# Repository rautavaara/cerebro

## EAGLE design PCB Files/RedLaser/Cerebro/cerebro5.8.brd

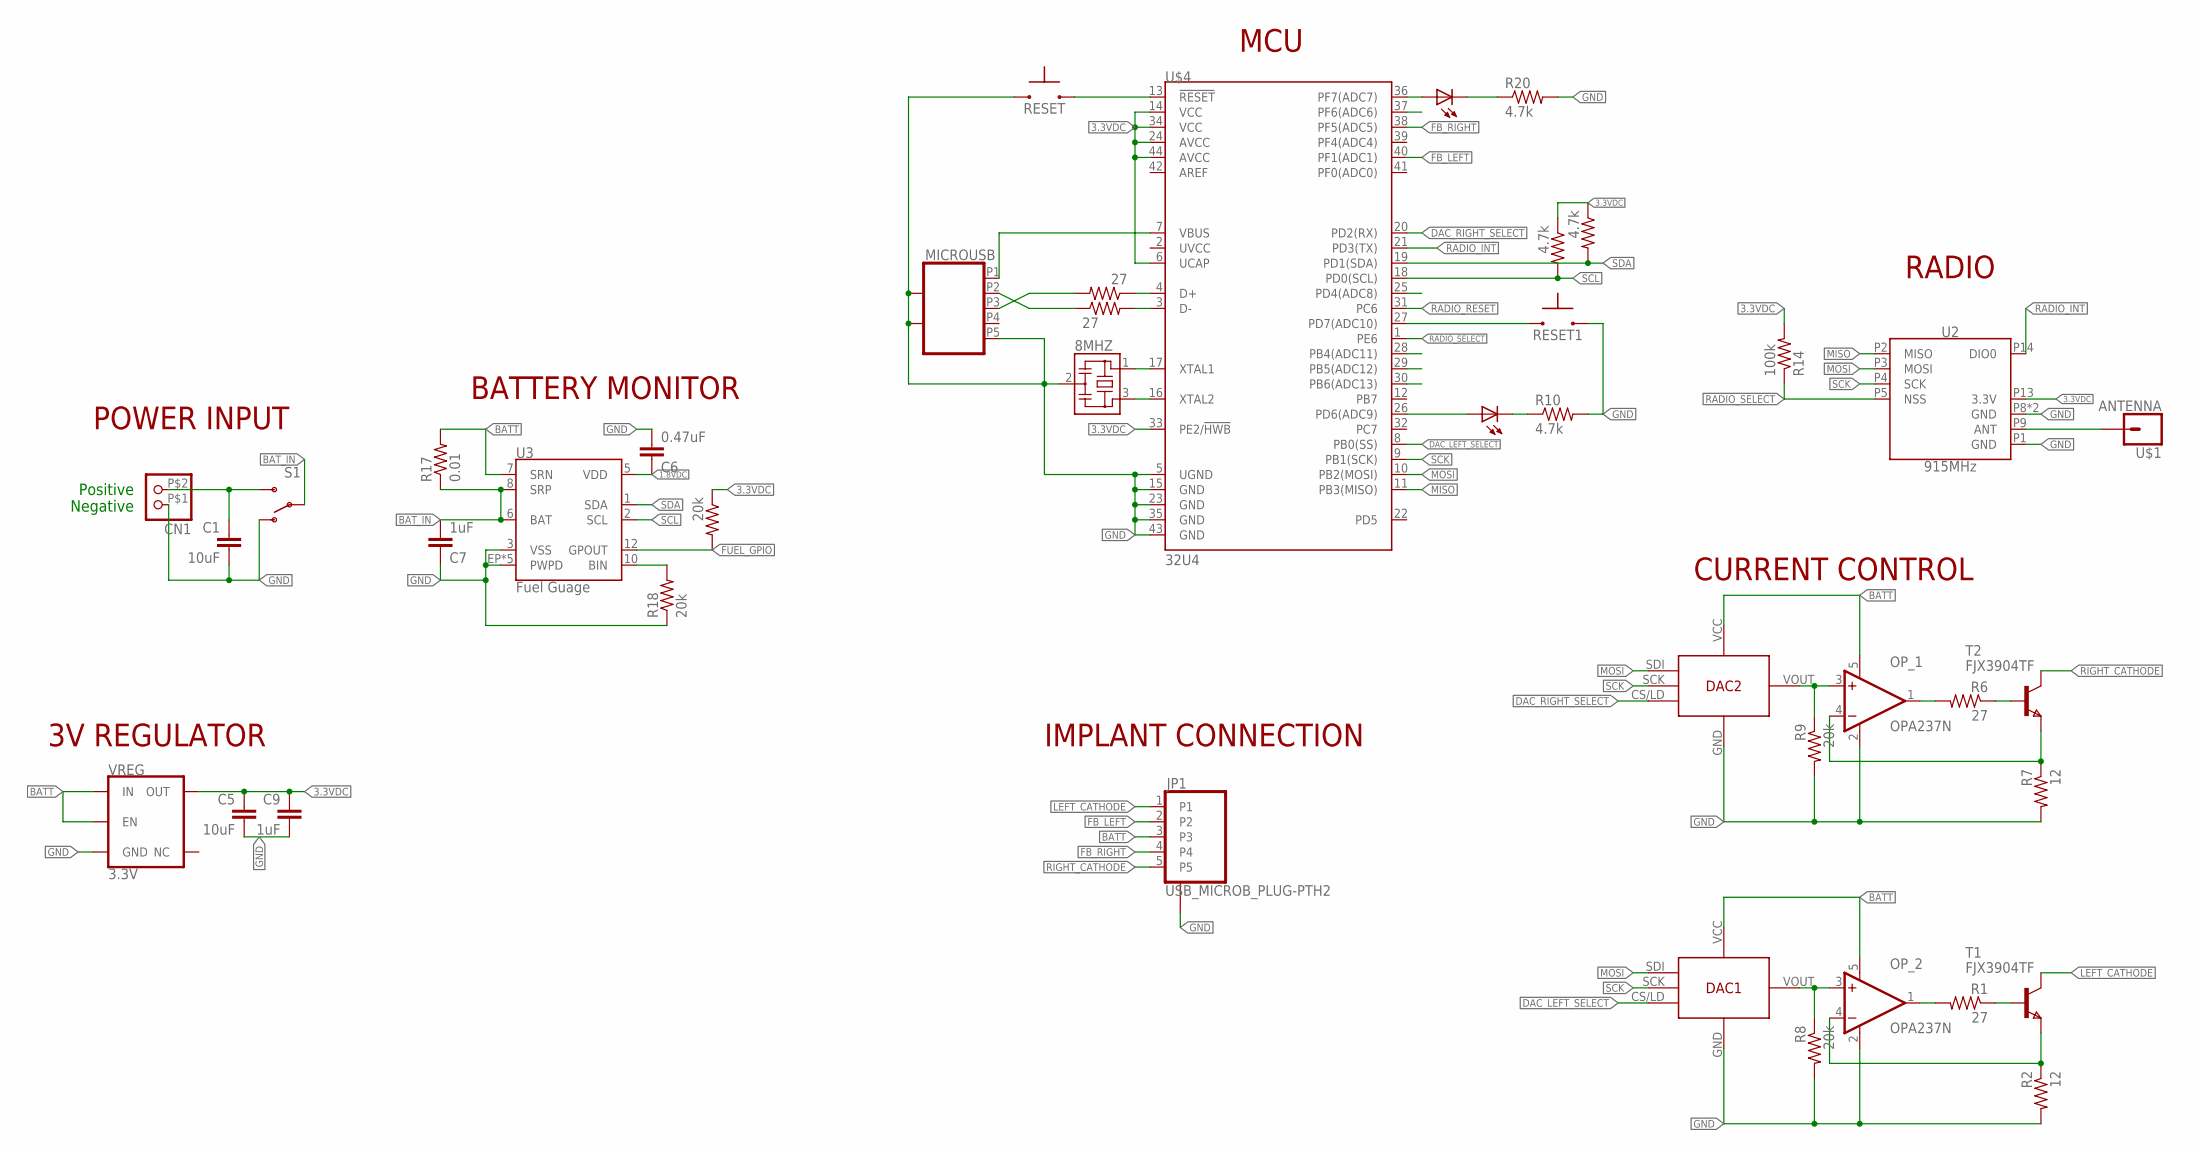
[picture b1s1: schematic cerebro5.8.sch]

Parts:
8MHZ: RESONATOR_CSTCE_V; CSTCE_V
C1, C5: 10uF; 0805
C6: 0.47uF; 0805
C7, C9: 1uF; 0805
CN1: JST_2PINMICRO; MICRO_LOCK_2PIN
DAC1, DAC2: DAC; SC-70
INDICATOR_LED1: YLW; CHIP-LED0603
INDICATOR_LED2: GRN; CHIP-LED0603
JP1: USB_MICROB_PLUG-PTH2; MICRO-B-TH
MICROUSB: USB_MICRO_SOCKET_HORZ_REINFORCED; USB_HORZ_REINFORCED_MICRO
OP_1, OP_2: OPA237N; SOT23-5
R1, R6, R12, R13: 27; 0603-RES
R2, R7: 12; 0603-RES
R8, R9, R18, R19: 20k; 0603-RES
R10, R15, R16, R20: 4.7k; 0603-RES
R14: 100k; 0603-RES
R17: 0.01; 1206
RESET, RESET1: SWITCH-MOMENTARY-NO; SWITCH_MOMENTARY_XS
S1: SWITCH-SPDTREINFORCED_SMD; SWITCH-SPDT-SMD-REINFORCED
T1, T2: FJX3904TF; SOT323
U2: 915MHz; RFM69HCW-XXXS2
U3: Fuel Guage; PDSO-N12
U$1: ANTENNA; 1X01
U$4: 32U4; QFN-44-NOPAD
VREG: 3.3V; SOT23-5

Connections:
1.8VDC: C6.1, U3.5 (VDD)
3.3VDC: C5.1, C9.1, R14.2, R15.1, R16.1, R19.1, U2.P13 (3.3V), U$4.6 (UCAP), U$4.14 (VCC), U$4.24 (AVCC), U$4.33 (PE2/!HWB), U$4.34 (VCC), U$4.44 (AVCC), VREG.5 (OUT)
BATT: DAC1.VCC (VIN), DAC2.VCC (VIN), JP1.3, OP_1.5 (V+), OP_2.5 (V+), R17.2, U3.7 (SRN), VREG.1 (IN), VREG.3 (EN)
BAT_IN: C7.2, R17.1, S1.2, U3.6 (BAT), U3.8 (SRP)
DAC_LEFT_SELECT: DAC1.CS/LD, U$4.8 (PB0(SS))
DAC_RIGHT_SELECT: DAC2.CS/LD, U$4.20 (PD2(RX))
FB_LEFT: JP1.2, U$4.40 (PF1(ADC1))
FB_RIGHT: JP1.4, U$4.38 (PF5(ADC5))
FUEL_GPIO: R19.2, U3.12 (GPOUT)
GND: 8MHZ.2, C1.2, C5.2, C6.2, C7.1, C9.2, CN1.P$1 (1), DAC1.GND, DAC2.GND, JP1.P$1 (GND_PINS), JP1.P$2 (GND_PINS), MICROUSB.G1, MICROUSB.G2, MICROUSB.P5, MICROUSB.P$1, MICROUSB.P$2, OP_1.2 (V-), OP_2.2 (V-), R2.2, R7.2, R8.2, R9.2, R10.2, R18.1, R20.2, RESET.P$1 (1), RESET1.P$2 (2), S1.1 (O), U2.P1 (GND), U2.P8 (GND), U2.P10 (GND), U3.3 (VSS), U3.EP (PWPD), U3.EP1 (PWPD), U3.EP2 (PWPD), U3.EP3 (PWPD), U3.EP4 (PWPD), U$4.5 (UGND), U$4.15 (GND), U$4.23 (GND), U$4.35 (GND), U$4.43 (GND), VREG.2 (GND)
LEFT_CATHODE: JP1.1, T1.1 (C)
MISO: U2.P2 (MISO), U$4.11 (PB3(MISO))
MOSI: DAC1.SDI, DAC2.SDI, U2.P3 (MOSI), U$4.10 (PB2(MOSI))
unnamed: DAC2.VOUT, OP_1.3 (+IN), R9.1
unnamed: OP_1.4 (-IN), R7.1, T2.3 (E)
unnamed: DAC1.VOUT, OP_2.3 (+IN), R8.1
unnamed: C1.1, CN1.P$2 (2), S1.3 (S)
unnamed: OP_1.1 (OUT), R6.2
unnamed: OP_2.4 (-IN), R2.1, T1.3 (E)
unnamed: R6.1, T2.2 (B)
unnamed: OP_2.1 (OUT), R1.2
unnamed: R1.1, T1.2 (B)
unnamed: 8MHZ.1, U$4.17 (XTAL1)
unnamed: 8MHZ.3, U$4.16 (XTAL2)
unnamed: MICROUSB.P1, U$4.7 (VBUS)
unnamed: R12.1, U$4.4 (D+)
unnamed: R13.2, U$4.3 (D-)
unnamed: MICROUSB.P3, R12.2
unnamed: MICROUSB.P2, R13.1
unnamed: INDICATOR_LED2.C, R10.1
unnamed: RESET1.P$1 (1), U$4.27 (PD7(ADC10))
unnamed: U2.P9 (ANT), U$1.1
unnamed: INDICATOR_LED1.C, R20.1
unnamed: INDICATOR_LED1.A, U$4.36 (PF7(ADC7))
unnamed: R18.2, U3.10 (BIN)
unnamed: INDICATOR_LED2.A, U$4.26 (PD6(ADC9))
RADIO_INT: U2.P14 (DIO0), U$4.21 (PD3(TX))
RADIO_RESET: U$4.31 (PC6)
RADIO_SELECT: R14.1, U2.P5 (NSS), U$4.1 (PE6)
RESET: RESET.P$2 (2), U$4.13 (!RESET)
RIGHT_CATHODE: JP1.5, T2.1 (C)
SCK: DAC1.SCK, DAC2.SCK, U2.P4 (SCK), U$4.9 (PB1(SCK))
SCL: R15.2, U3.2 (SCL), U$4.18 (PD0(SCL))
SDA: R16.2, U3.1 (SDA), U$4.19 (PD1(SDA))

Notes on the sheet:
Positive
Negative
CURRENT CONTROL
RADIO
3V REGULATOR
BATTERY MONITOR
POWER INPUT
IMPLANT CONNECTION
MCU

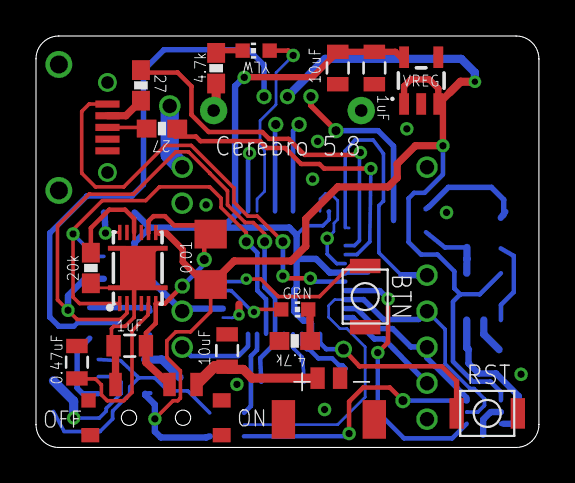
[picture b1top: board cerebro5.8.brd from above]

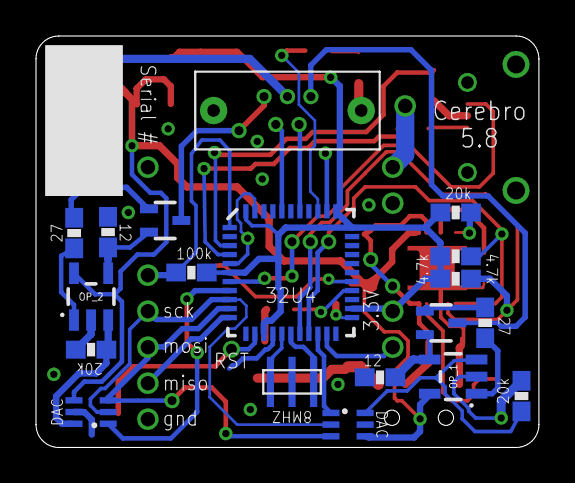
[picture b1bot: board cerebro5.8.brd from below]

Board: 2 copper layers, 27.9 x 22.9 mm, 41 parts (19 on the bottom side), 43 nets.

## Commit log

2021-06-09 Red Laser modifications. Deleted boost circuit
